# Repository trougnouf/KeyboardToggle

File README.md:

# KeyboardToggle
Physical switch to turn USB keyboard (or anything) on or off (WIP)

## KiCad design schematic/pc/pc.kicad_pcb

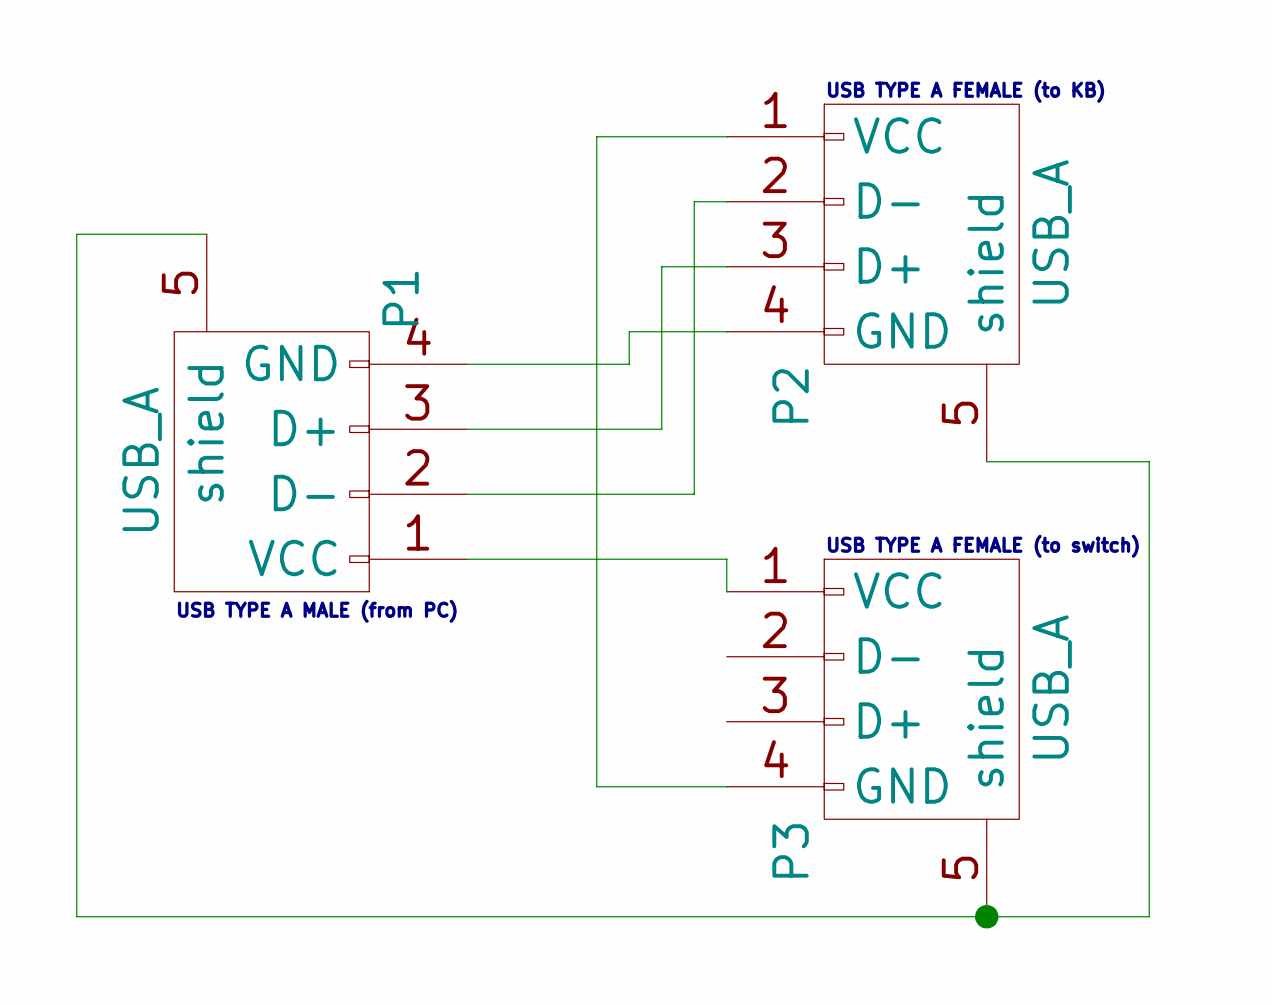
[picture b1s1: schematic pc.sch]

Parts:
P1, P2, P3: USB_A

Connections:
unnamed: P1.1 (VCC), P3.1 (VCC)
unnamed: P1.2 (D-), P2.2 (D-)
unnamed: P1.3 (D+), P2.3 (D+)
unnamed: P1.4 (GND), P2.4 (GND)
unnamed: P1.5 (shield), P2.5 (shield), P3.5 (shield)
unnamed: P2.1 (VCC), P3.4 (GND)

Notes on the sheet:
USB TYPE A MALE (from PC)
USB TYPE A FEMALE (to KB)
USB TYPE A FEMALE (to switch)

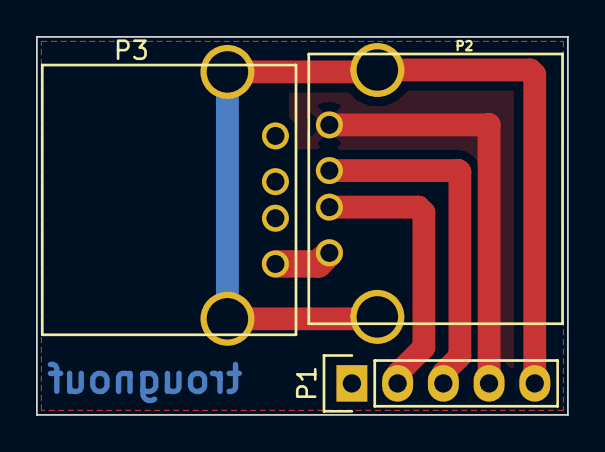
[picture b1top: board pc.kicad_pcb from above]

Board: 2 copper layers, 29.5 x 21.0 mm, 3 parts (0 on the bottom side), 6 nets.

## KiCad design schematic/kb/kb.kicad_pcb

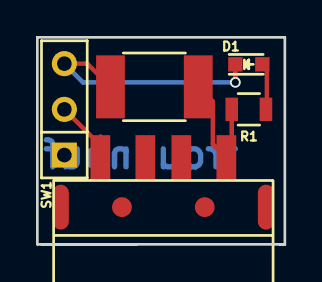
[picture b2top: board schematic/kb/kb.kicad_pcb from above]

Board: 2 copper layers, 13.8 x 11.5 mm, 5 parts (0 on the bottom side), 4 nets.

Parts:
D1: LED; LED-0603
P1: USB_A
R1: 150; R_0805
R2: PPTC; R_1812
SW1: Switch_SPDT_x2; SW_Micro_SPST

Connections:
unnamed: D1.1, R2.1, SW1.3
unnamed: D1.2, R1.2
unnamed: P1.1, R1.1, R2.2
unnamed: P1.4, SW1.2

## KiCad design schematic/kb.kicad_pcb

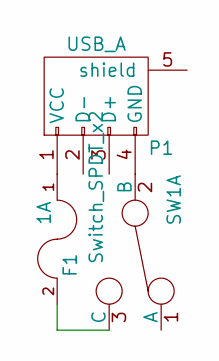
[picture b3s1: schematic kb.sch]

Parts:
F1: 1A; C_0603
P1: USB_A
SW1: Switch_SPDT_x2; SW_Micro_SPST

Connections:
unnamed: F1.1, P1.1 (VCC)
unnamed: F1.2, SW1.3 (C)
unnamed: P1.4 (GND), SW1.2 (B)

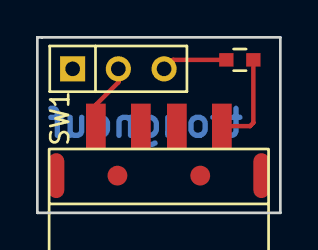
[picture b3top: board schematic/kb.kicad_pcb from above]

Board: 2 copper layers, 13.5 x 9.8 mm, 3 parts (0 on the bottom side), 3 nets.

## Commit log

2016-01-03 Added schematic and pcb for the USB switch
2016-01-03 Organized files
2016-01-03 Replaced single use fuse with resettable fuse (PPTC) on the keyboard-side adapter
2016-01-05 Added a red LED and matching resistor to warn user when USB splitter is missing
2016-01-05 Better fit for the text
2016-01-07 Switched PC board to wired male
2016-01-07 screenshot
